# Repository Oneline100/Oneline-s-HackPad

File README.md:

# Oneline's Hackpad
This a Hackpad that I have been working on for sometime for studying, video editing, gaming and voice chat. 

## Renders:

## Features
- 6 Key Marcopad
  - Can Switch to diffrent layouts for diffrent task
* OLED screen for diffent modes and animations
+ LEDs for color and checking for power.

## Specifications
BOM:
- 1x Seeed XIAO RP2040 (SMD Mounted)
- 6x Cherry MX Switches
- 2x SK6812 MINI Leds
- 1x 0.91 inch OLED display
- 6x Blank DSA Keycaps
- 4x M3x16mm screws
- 4x M3 Heatset

Tools:
- 3D Printer
- Soldering Iron

Custom Parts
- 1x Back Case
- 1x Front Case
- 1x PCB

## CAD Model
> [!NOTE]
> This is my first time using Fusion. I used to using OnShape but Fusion was great experience to learn and use!

## PCB and Wiring
> [!NOTE]
> Same thing as the Fusion, make my first PCB was a challenge! After watching many videos and websites, I was able to get this working

> [!IMPORTANT]
> DRC was run and all tests have been passed! Yay!

| Schematic  | PCB | 3D Model
| ------------- | ------------- | ------------- |
||||

> [!NOTE]
> Code now works and its goods!

The firmware uses the code provied and some other feautres and libaries to get this working. Controls the keys, leds, and screen.

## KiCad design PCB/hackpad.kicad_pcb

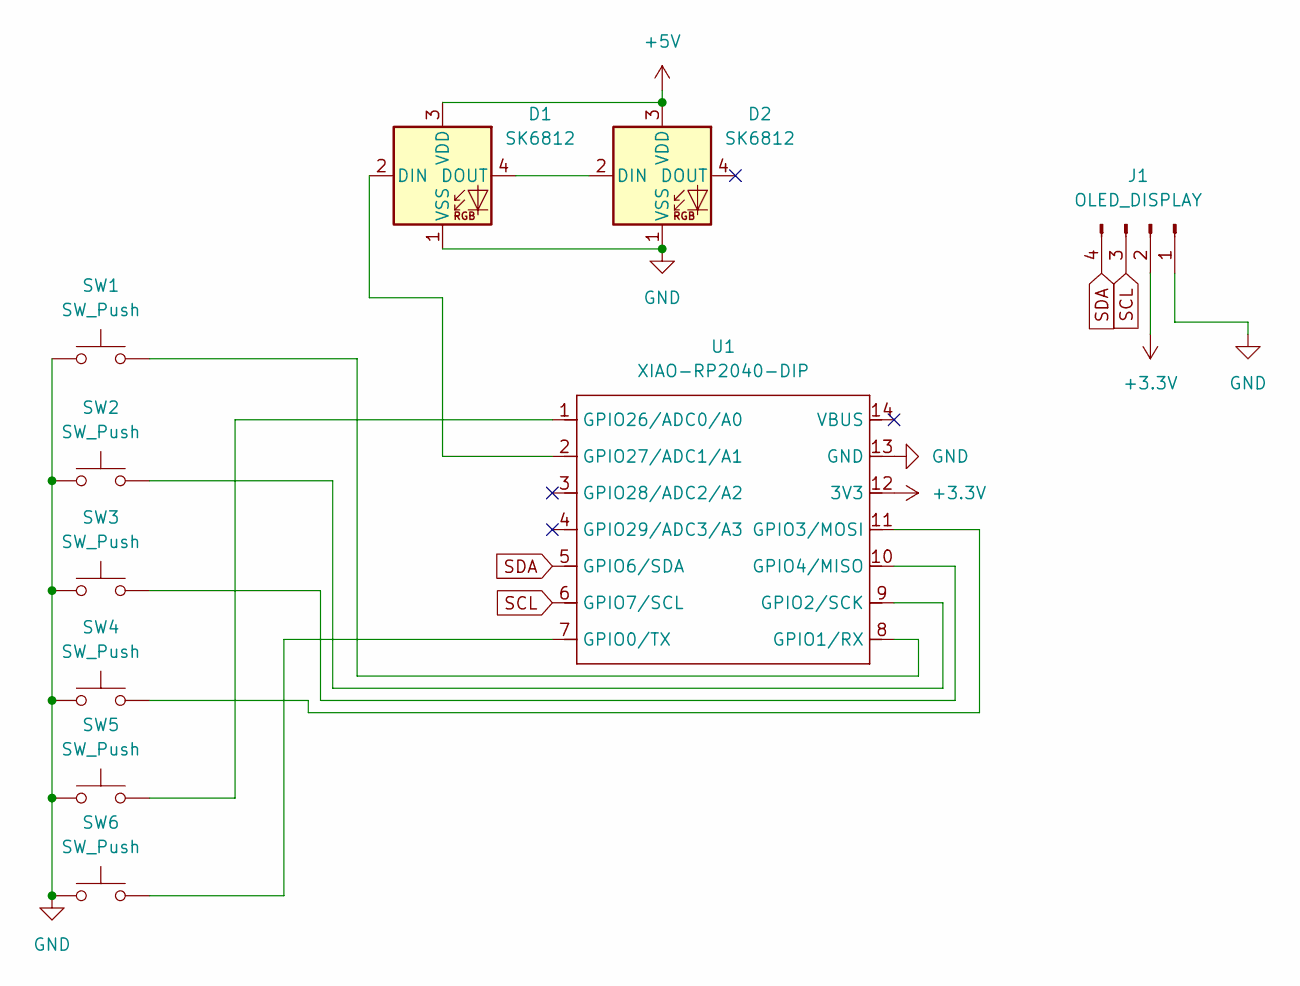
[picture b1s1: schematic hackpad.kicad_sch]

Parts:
D1, D2: SK6812; LED_SK6812MINI_PLCC4_3.5x3.5mm_P1.75mm
J1: OLED_DISPLAY; SSD1306-0.91-OLED-4pin-128x32
SW1, SW2, SW3, SW4, SW5, SW6: SW_Push; SW_Cherry_MX_1.00u_PCB
U1: XIAO-RP2040-DIP

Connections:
+3.3V: J1.2, U1.12 (3V3)
+5V: D1.3 (VDD), D2.3 (VDD)
GND: D1.1 (VSS), D2.1 (VSS), J1.1, SW1.1, SW2.1, SW3.1, SW4.1, SW5.1, SW6.1, U1.13 (GND)
unnamed: D1.2 (DIN), U1.2 (GPIO27/ADC1/A1)
unnamed: D1.4 (DOUT), D2.2 (DIN)
unnamed: SW6.2, U1.7 (GPIO0/TX)
unnamed: SW1.2, U1.8 (GPIO1/RX)
unnamed: SW2.2, U1.9 (GPIO2/SCK)
unnamed: SW4.2, U1.11 (GPIO3/MOSI)
unnamed: SW3.2, U1.10 (GPIO4/MISO)
unnamed: SW5.2, U1.1 (GPIO26/ADC0/A0)
SCL: J1.3, U1.6 (GPIO7/SCL)
SDA: J1.4, U1.5 (GPIO6/SDA)

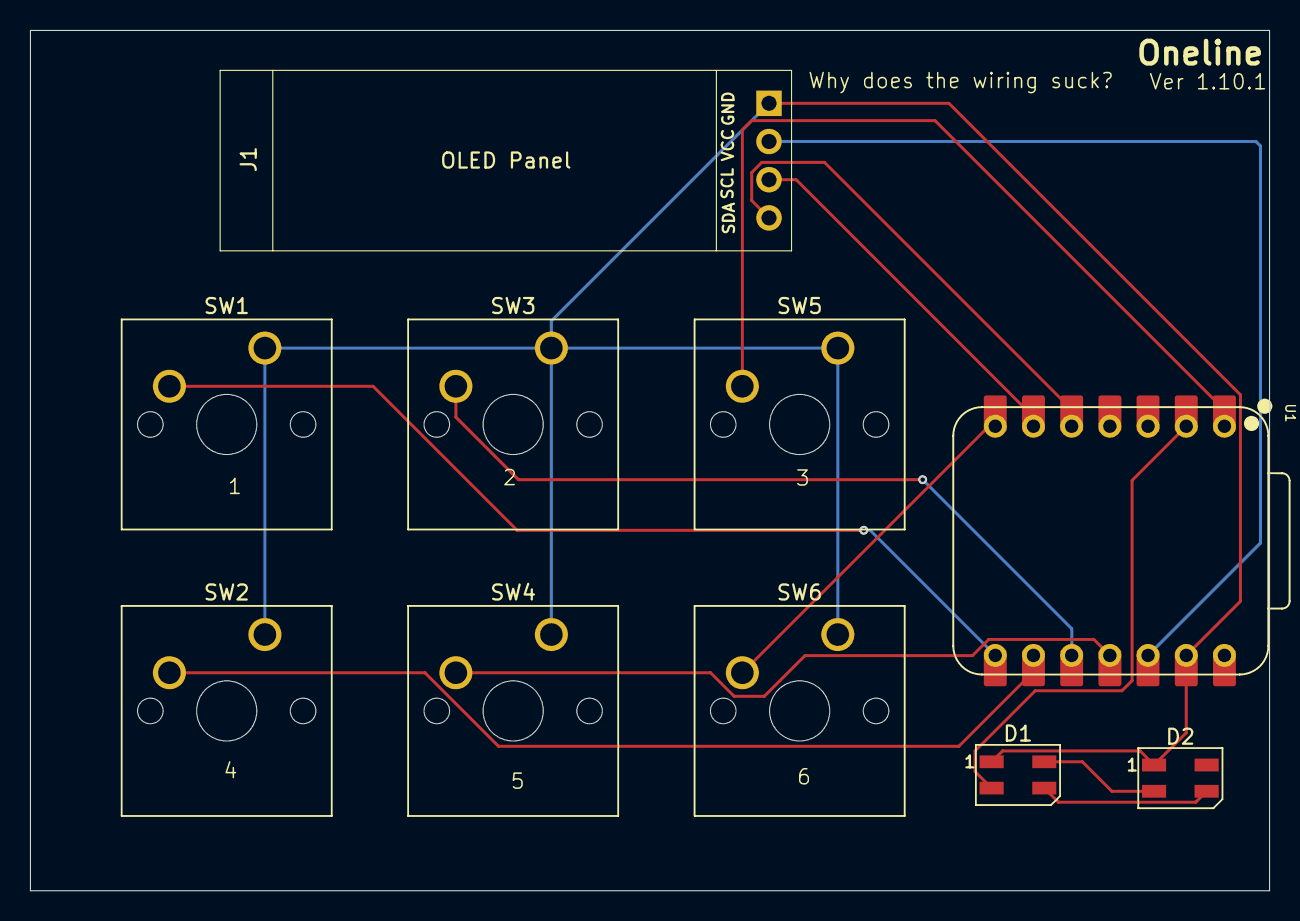
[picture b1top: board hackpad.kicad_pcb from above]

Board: 2 copper layers, 82.4 x 57.2 mm, 10 parts (0 on the bottom side), 13 nets.

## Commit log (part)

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2026-01-10 main upload
2026-01-11 Add Images
2026-01-12 Revision 2V
2026-03-06 Update main.py
    Fixed everything and added more to the firmware
2026-03-07 Update main.py
    More functions and UI
